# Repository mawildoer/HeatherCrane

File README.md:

# HeatherCrane

The goal of this project is to provide independence through mobility to the sevearly disabled.

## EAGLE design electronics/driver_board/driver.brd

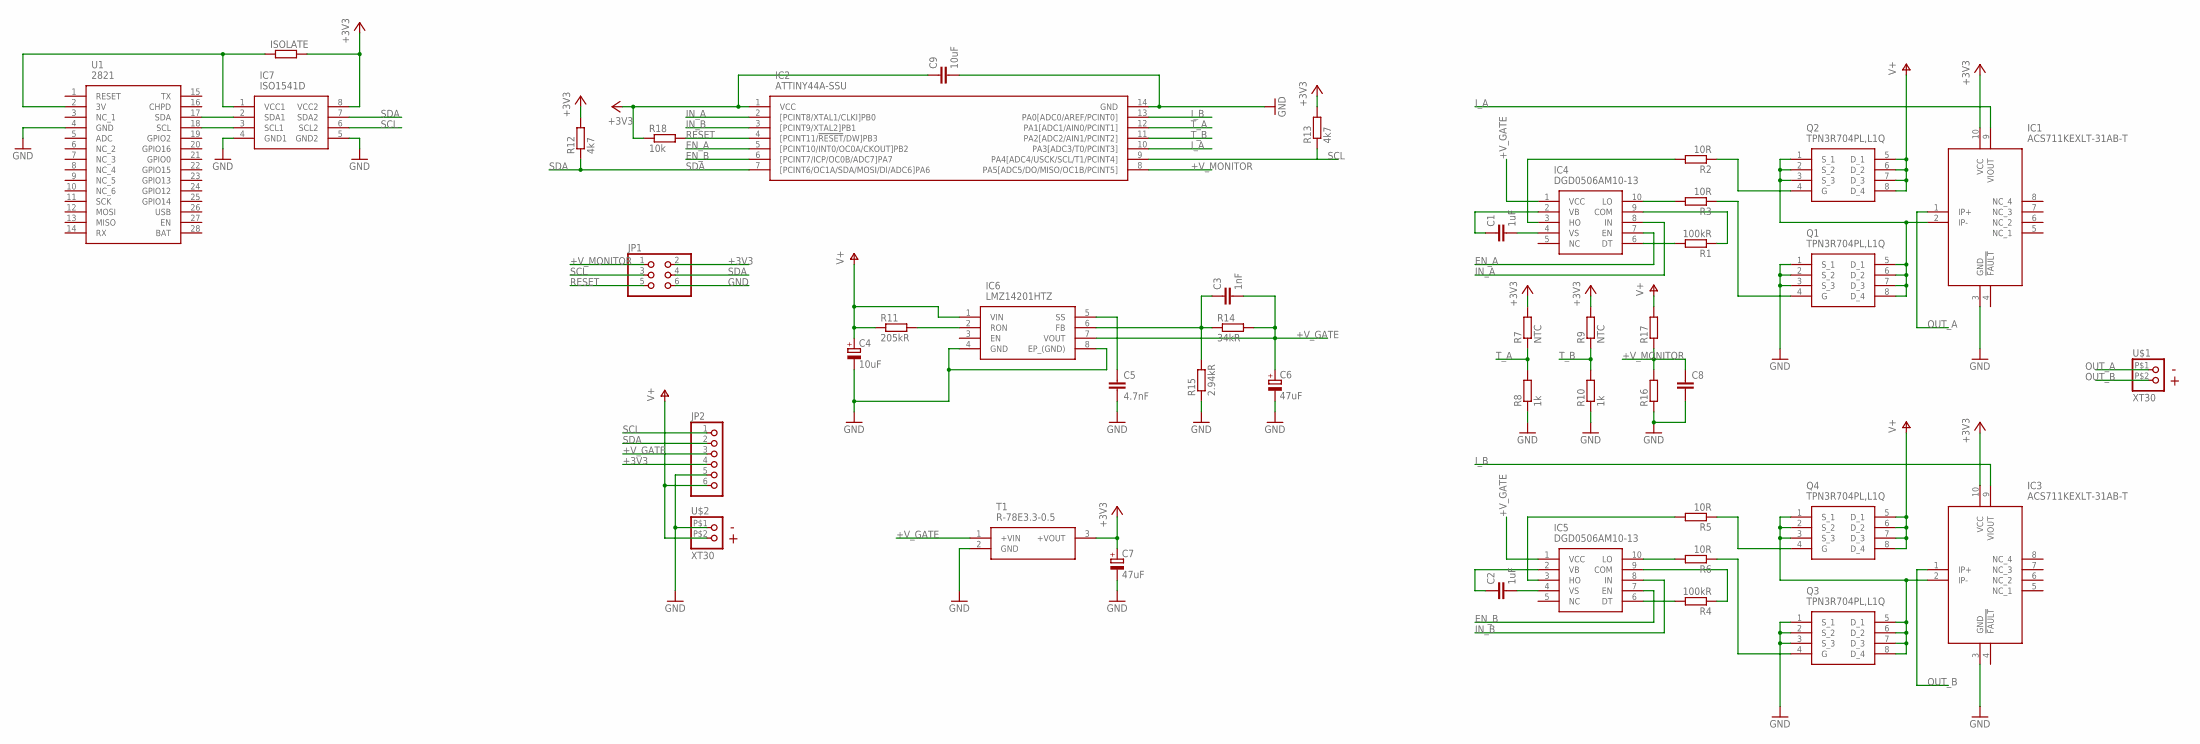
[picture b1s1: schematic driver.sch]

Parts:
C1, C2: 1uF; C0603
C3: 1nF; C0603
C4: 10uF; E2,5-6E
C5: 4.7nF; C0603
C6, C7: 47uF; E2,5-6E
C8: C-EUC0603; C0603
C9: 10uF; C0603
IC1, IC3: ACS711KEXLT-31AB-T; EX-PACKAGE
IC2: ATTINY44A-SSU; SOIC127P600X175-14N
IC4, IC5: DGD0506AM10-13; SOP50P490X110-10N
IC6: LMZ14201HTZ; NDW0007A
IC7: ISO1541D; SOIC127P600X175-8N
ISOLATE: R-EU_R0805; R0805
JP1: PINHD-2X3; 2X03
JP2: PINHD-1X6; 1X06
Q1, Q2, Q3, Q4: TPN3R704PL,L1Q; TSON_ADVANCE
R1, R4: 100kR; R0603
R2, R3, R5, R6: 10R; R0603
R7, R9: NTC; R0603
R8, R10: 1k; R0603
R11: 205kR; R0603
R12, R13: 4k7; R0603
R14: 34kR; R0603
R15: 2.94kR; R0603
R16, R17: R-EU_R0603; R0603
R18: 10k; R0603
T1: R-78E3.3-0.5; SHDRV3W100P0_254_1X3_1160X850X
U1: 2821
U$1, U$2: XT30

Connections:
+3V3: C7.+, C9.1, IC1.10 (VCC), IC2.1 (VCC), IC3.10 (VCC), IC7.8 (VCC2), ISOLATE.2, JP1.2, JP2.4, R7.2, R9.2, R12.2, R13.2, R18.1, T1.3 (+VOUT)
+V_GATE: C3.2, C6.+, IC4.1 (VCC), IC5.1 (VCC), IC6.7 (VOUT), JP2.3, R14.2, T1.1 (+VIN)
+V_MONITOR: C8.1, IC2.8 (PA5[ADC5/DO/MISO/OC1B/PCINT5]), JP1.1, R16.2, R17.1
EN_A: IC2.5 ([PCINT10/INT0/OC0A/CKOUT]PB2), IC4.7 (EN)
EN_B: IC2.6 ([PCINT7/ICP/OC0B/ADC7]PA7), IC5.7 (EN)
GND: C4.-, C5.2, C6.-, C7.-, C8.2, C9.2, IC1.3 (GND), IC2.14 (GND), IC3.3 (GND), IC6.4 (GND), IC6.8 (EP_(GND)), IC7.4 (GND1), IC7.5 (GND2), JP1.6, JP2.5, Q1.1 (S_1), Q1.2 (S_2), Q1.3 (S_3), Q3.1 (S_1), Q3.2 (S_2), Q3.3 (S_3), R8.1, R10.1, R15.1, R16.1, T1.2 (GND), U1.4 (GND), U$2.P$1 (1)
IN_A: IC2.2 ([PCINT8/XTAL1/CLKI]PB0), IC4.8 (IN)
IN_B: IC2.3 ([PCINT9/XTAL2]PB1), IC5.8 (IN)
I_A: IC1.9 (VIOUT), IC2.10 (PA3[ADC3/T0/PCINT3])
I_B: IC2.13 (PA0[ADC0/AREF/PCINT0]), IC3.9 (VIOUT)
unnamed: IC3.2 (IP-), Q3.5 (D_1), Q3.6 (D_2), Q3.7 (D_3), Q3.8 (D_4), Q4.1 (S_1), Q4.2 (S_2), Q4.3 (S_3)
unnamed: Q2.4 (G), R2.1
unnamed: C1.2, IC4.4 (VS)
unnamed: C1.1, IC4.2 (VB)
unnamed: Q4.4 (G), R5.1
unnamed: IC1.2 (IP-), Q1.5 (D_1), Q1.6 (D_2), Q1.7 (D_3), Q1.8 (D_4), Q2.1 (S_1), Q2.2 (S_2), Q2.3 (S_3)
unnamed: Q1.4 (G), R3.1
unnamed: IC4.6 (DT), R1.2
unnamed: IC4.9 (COM), R1.1
unnamed: IC4.3 (HO), R2.2
unnamed: IC4.10 (LO), R3.2
unnamed: C2.2, IC5.4 (VS)
unnamed: C2.1, IC5.2 (VB)
unnamed: Q3.4 (G), R6.1
unnamed: IC5.6 (DT), R4.2
unnamed: IC5.9 (COM), R4.1
unnamed: IC5.3 (HO), R5.2
unnamed: IC5.10 (LO), R6.2
unnamed: IC7.2 (SDA1), U1.17 (SDA)
unnamed: IC6.2 (RON), R11.2
unnamed: C3.1, IC6.6 (FB), R14.1, R15.2
unnamed: C5.1, IC6.5 (SS)
unnamed: IC7.3 (SCL1), U1.18 (SCL)
unnamed: IC7.1 (VCC1), ISOLATE.1, U1.2 (3V)
OUT_A: IC1.1 (IP+), U$1.P$1 (1)
OUT_B: IC3.1 (IP+), U$1.P$2 (2)
RESET: IC2.4 ([PCINT11/!RESET!/DW]PB3), JP1.5, R18.2
SCL: IC2.9 (PA4[ADC4/USCK/SCL/T1/PCINT4]), IC7.6 (SCL2), JP1.3, JP2.1, R13.1
SDA: IC2.7 ([PCINT6/OC1A/SDA/MOSI/DI/ADC6]PA6), IC7.7 (SDA2), JP1.4, JP2.2, R12.1
T_A: IC2.12 (PA1[ADC1/AIN0/PCINT1]), R7.1, R8.2
T_B: IC2.11 (PA2[ADC2/AIN1/PCINT2]), R9.1, R10.2
V+: C4.+, IC6.1 (VIN), JP2.6, Q2.5 (D_1), Q2.6 (D_2), Q2.7 (D_3), Q2.8 (D_4), Q4.5 (D_1), Q4.6 (D_2), Q4.7 (D_3), Q4.8 (D_4), R11.1, R17.2, U$2.P$2 (2)

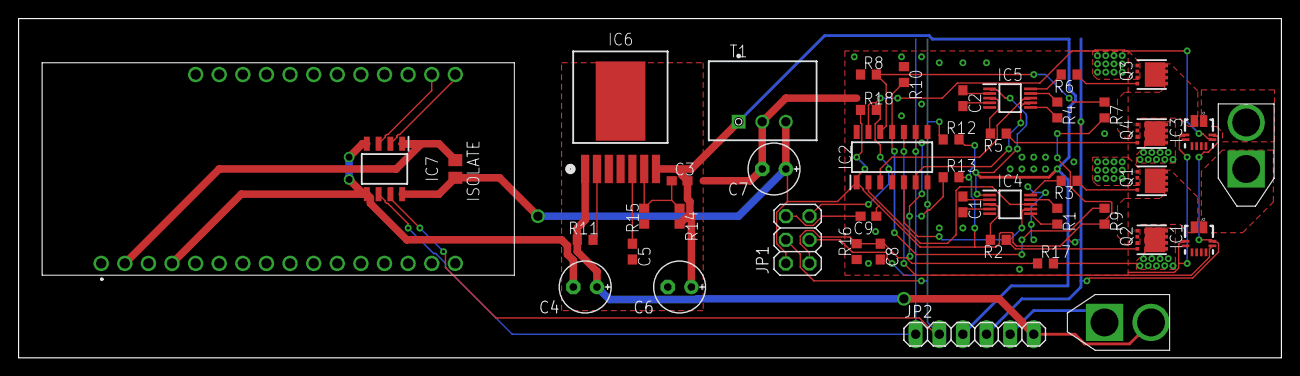
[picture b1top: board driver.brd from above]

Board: 2 copper layers, 135.9 x 36.5 mm, 45 parts (0 on the bottom side), 42 nets.

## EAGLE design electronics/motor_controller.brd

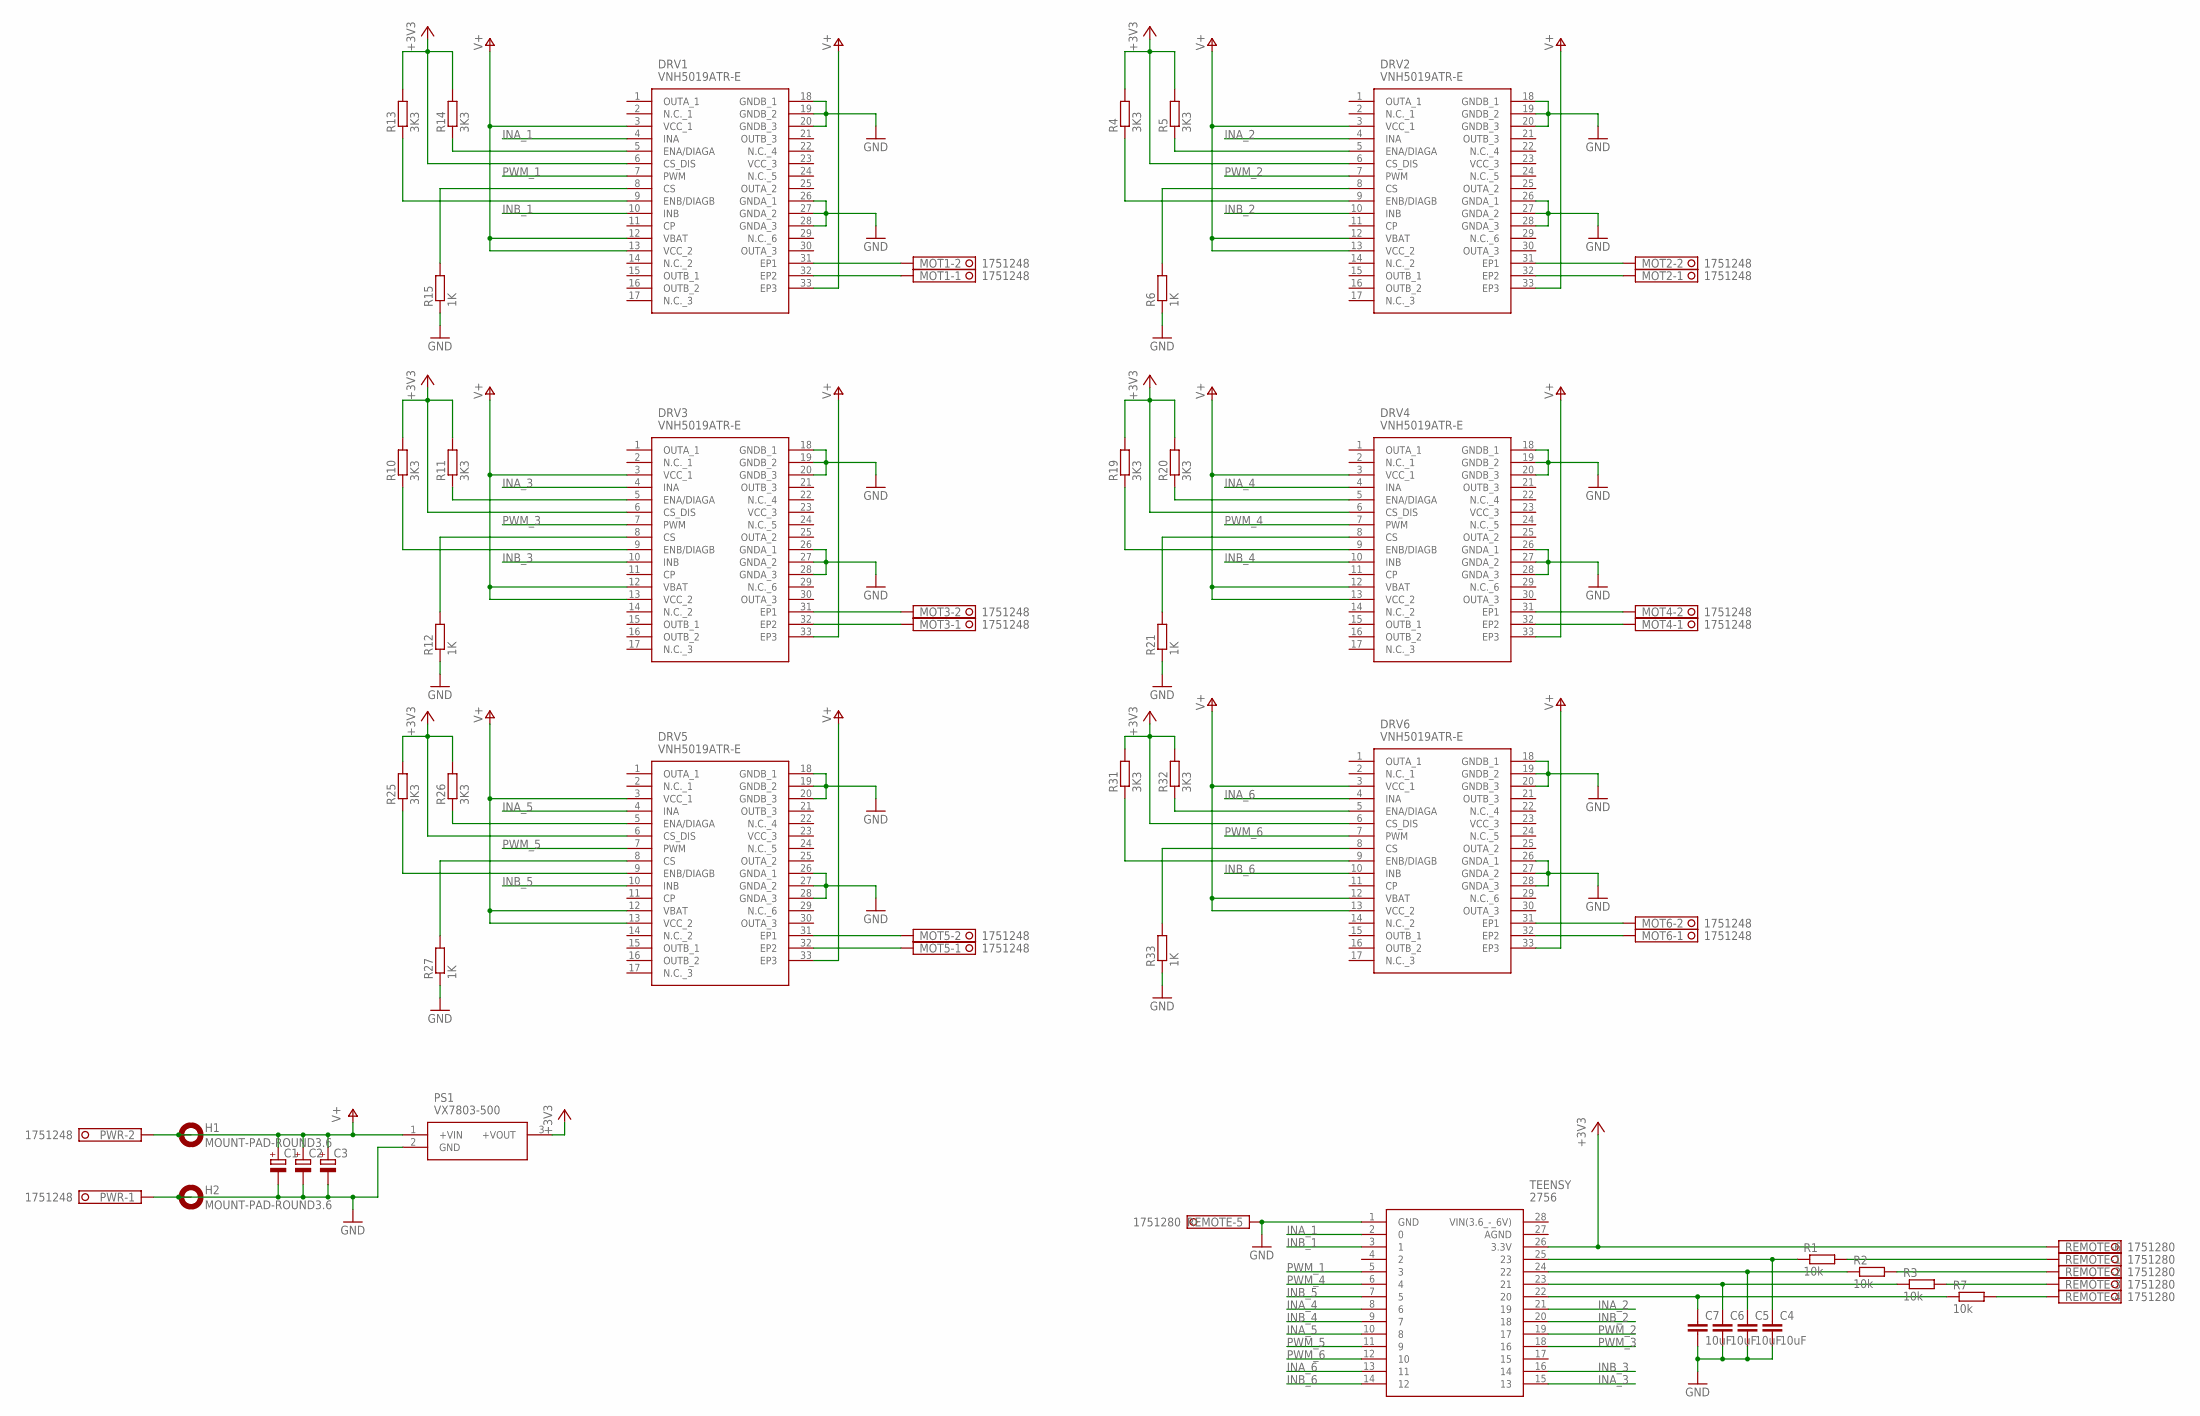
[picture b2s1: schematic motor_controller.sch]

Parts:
C1, C2, C3: CPOL-EUE10-20; EB20D
C4, C5, C6, C7: 10uF; C0603
DRV1, DRV2, DRV3, DRV4, DRV5, DRV6: VNH5019ATR-E; VNH5019A-E_1
H1, H2: MOUNT-PAD-ROUND3.6; 3,6-PAD
MOT1, MOT2, MOT3, MOT4, MOT5, MOT6: 1751248
PS1: VX7803-500; VX7805500
PWR: 1751248
R1, R2, R3, R7: 10k; R0603
R4, R5, R10, R11, R13, R14, R19, R20, R25, R26, R31, R32: 3K3; R0603
R6, R12, R15, R21, R27, R33: 1K; R0603
REMOTE: 1751280
TEENSY: 2756; DIP1500W100P250L3500H700Q28N

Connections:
+3V3: DRV1.6 (CS_DIS), DRV2.6 (CS_DIS), DRV3.6 (CS_DIS), DRV4.6 (CS_DIS), DRV5.6 (CS_DIS), DRV6.6 (CS_DIS), PS1.3 (+VOUT), R4.2, R5.2, R10.2, R11.2, R13.2, R14.2, R19.2, R20.2, R25.2, R26.2, R31.2, R32.2, REMOTE.6, TEENSY.26 (3.3V)
AGND: TEENSY.27 (AGND)
GND: C1.-, C2.-, C3.-, C4.2, C5.2, C6.2, C7.2, DRV1.18 (GNDB_1), DRV1.19 (GNDB_2), DRV1.20 (GNDB_3), DRV1.26 (GNDA_1), DRV1.27 (GNDA_2), DRV1.28 (GNDA_3), DRV2.18 (GNDB_1), DRV2.19 (GNDB_2), DRV2.20 (GNDB_3), DRV2.26 (GNDA_1), DRV2.27 (GNDA_2), DRV2.28 (GNDA_3), DRV3.18 (GNDB_1), DRV3.19 (GNDB_2), DRV3.20 (GNDB_3), DRV3.26 (GNDA_1), DRV3.27 (GNDA_2), DRV3.28 (GNDA_3), DRV4.18 (GNDB_1), DRV4.19 (GNDB_2), DRV4.20 (GNDB_3), DRV4.26 (GNDA_1), DRV4.27 (GNDA_2), DRV4.28 (GNDA_3), DRV5.18 (GNDB_1), DRV5.19 (GNDB_2), DRV5.20 (GNDB_3), DRV5.26 (GNDA_1), DRV5.27 (GNDA_2), DRV5.28 (GNDA_3), DRV6.18 (GNDB_1), DRV6.19 (GNDB_2), DRV6.20 (GNDB_3), DRV6.26 (GNDA_1), DRV6.27 (GNDA_2), DRV6.28 (GNDA_3), H2.B3,6, PS1.2 (GND), PWR.1, R6.1, R12.1, R15.1, R21.1, R27.1, R33.1, REMOTE.5, TEENSY.1 (GND)
INA_1: DRV1.4 (INA), TEENSY.2 (0)
INA_2: DRV2.4 (INA), TEENSY.21 (19)
INA_3: DRV3.4 (INA), TEENSY.15 (13)
INA_4: DRV4.4 (INA), TEENSY.8 (6)
INA_5: DRV5.4 (INA), TEENSY.10 (8)
INA_6: DRV6.4 (INA), TEENSY.13 (11)
INB_1: DRV1.10 (INB), TEENSY.3 (1)
INB_2: DRV2.10 (INB), TEENSY.20 (18)
INB_3: DRV3.10 (INB), TEENSY.16 (14)
INB_4: DRV4.10 (INB), TEENSY.9 (7)
INB_5: DRV5.10 (INB), TEENSY.7 (5)
INB_6: DRV6.10 (INB), TEENSY.14 (12)
unnamed: C4.1, R1.1, TEENSY.25 (23)
unnamed: C5.1, R2.1, TEENSY.24 (22)
unnamed: C6.1, R3.1, TEENSY.23 (21)
unnamed: C7.1, R7.1, TEENSY.22 (20)
unnamed: R1.2, REMOTE.1
unnamed: DRV2.5 (ENA/DIAGA), R5.1
unnamed: DRV2.9 (ENB/DIAGB), R4.1
unnamed: DRV2.8 (CS), R6.2
unnamed: DRV2.31 (EP1), MOT2.2
unnamed: DRV2.32 (EP2), MOT2.1
unnamed: R2.2, REMOTE.2
unnamed: R3.2, REMOTE.3
unnamed: R7.2, REMOTE.4
unnamed: DRV3.5 (ENA/DIAGA), R11.1
unnamed: DRV3.9 (ENB/DIAGB), R10.1
unnamed: DRV3.8 (CS), R12.2
unnamed: DRV3.31 (EP1), MOT3.2
unnamed: DRV3.32 (EP2), MOT3.1
unnamed: DRV1.5 (ENA/DIAGA), R14.1
unnamed: DRV1.9 (ENB/DIAGB), R13.1
unnamed: DRV1.8 (CS), R15.2
unnamed: DRV1.31 (EP1), MOT1.2
unnamed: DRV1.32 (EP2), MOT1.1
unnamed: DRV4.5 (ENA/DIAGA), R20.1
unnamed: DRV4.9 (ENB/DIAGB), R19.1
unnamed: DRV4.8 (CS), R21.2
unnamed: DRV4.31 (EP1), MOT4.2
unnamed: DRV4.32 (EP2), MOT4.1
unnamed: DRV5.5 (ENA/DIAGA), R26.1
unnamed: DRV5.9 (ENB/DIAGB), R25.1
unnamed: DRV5.8 (CS), R27.2
unnamed: DRV5.31 (EP1), MOT5.2
unnamed: DRV5.32 (EP2), MOT5.1
unnamed: DRV6.5 (ENA/DIAGA), R32.1
unnamed: DRV6.9 (ENB/DIAGB), R31.1
unnamed: DRV6.8 (CS), R33.2
unnamed: DRV6.31 (EP1), MOT6.2
unnamed: DRV6.32 (EP2), MOT6.1
PWM_1: DRV1.7 (PWM), TEENSY.5 (3)
PWM_2: DRV2.7 (PWM), TEENSY.19 (17)
PWM_3: DRV3.7 (PWM), TEENSY.18 (16)
PWM_4: DRV4.7 (PWM), TEENSY.6 (4)
PWM_5: DRV5.7 (PWM), TEENSY.11 (9)
PWM_6: DRV6.7 (PWM), TEENSY.12 (10)
V+: C1.+, C2.+, C3.+, DRV1.3 (VCC_1), DRV1.12 (VBAT), DRV1.13 (VCC_2), DRV1.33 (EP3), DRV2.3 (VCC_1), DRV2.12 (VBAT), DRV2.13 (VCC_2), DRV2.33 (EP3), DRV3.3 (VCC_1), DRV3.12 (VBAT), DRV3.13 (VCC_2), DRV3.33 (EP3), DRV4.3 (VCC_1), DRV4.12 (VBAT), DRV4.13 (VCC_2), DRV4.33 (EP3), DRV5.3 (VCC_1), DRV5.12 (VBAT), DRV5.13 (VCC_2), DRV5.33 (EP3), DRV6.3 (VCC_1), DRV6.12 (VBAT), DRV6.13 (VCC_2), DRV6.33 (EP3), H1.B3,6, PS1.1 (+VIN), PWR.2
VIN(3.6_-_6V): TEENSY.28 (VIN(3.6_-_6V))

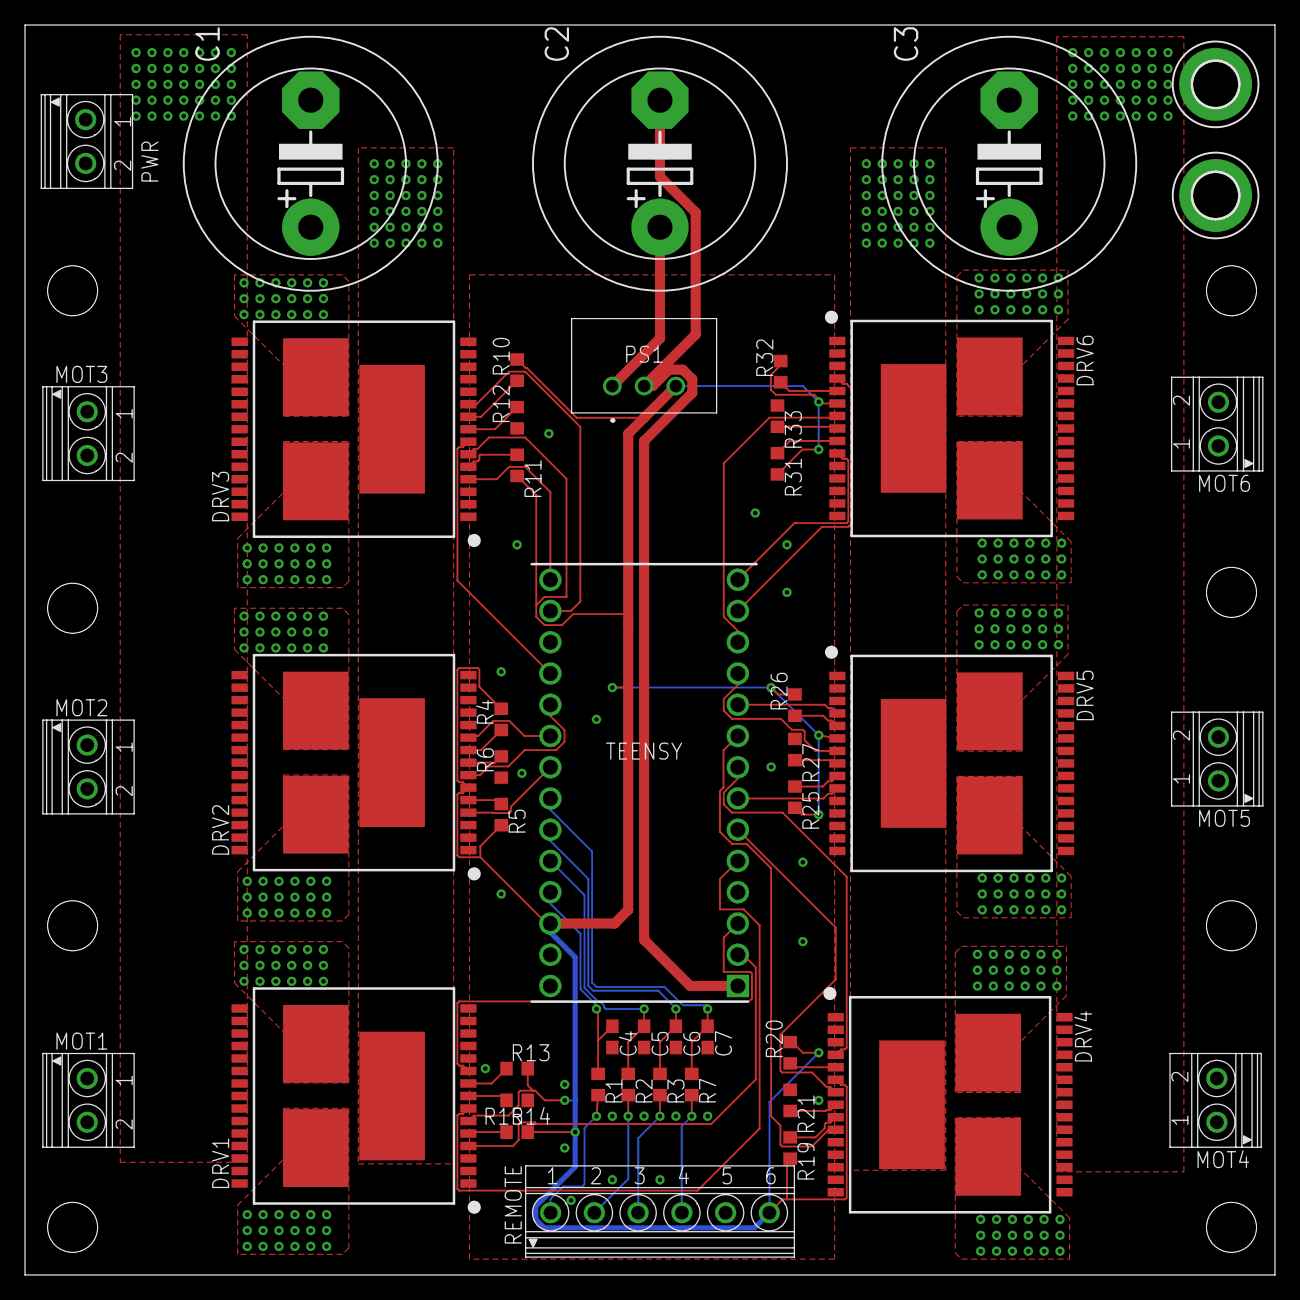
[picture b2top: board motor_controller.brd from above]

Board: 2 copper layers, 100.0 x 100.0 mm, 47 parts (0 on the bottom side), 59 nets.

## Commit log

2019-02-21 Motor Controller v1
    6 full bridge, 30A continuous integrated drivers which allow for control of the four wheels and the linear actuators from a Teensy LC. The inputs are low pass filtered and to reduce noise on the line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
2019-02-22 Design Review V1
    Changed the signal levels from V+ to 3V3 with 3K3 resistors
2019-03-01 Added digikey to BOM
2019-03-31 Joystick code self tuning added
2019-03-31 hbridge motor setup functions (as long as you select the right pins in software... ooops)
2019-03-31 Add admin ignore for receipts etc...
2019-04-05 OO joystick
2019-04-05 Tested and working libraries
2019-04-08 Software and core verified as functional. Requires hardware for final testing
2019-04-09 Added joystick mount
2019-04-19 Update mounting holes in joystick mount
2019-04-19 Tune software
2019-04-19 Add readme details
2019-04-19 Add video to readme
2019-04-19 Replace video with gif
2019-05-10 Driver Review
2019-05-11 For review 2
